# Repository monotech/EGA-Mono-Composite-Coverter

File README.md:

Based on Hugo Holden's "FITTING AN EGA CARD TO AN IBM 5155" from 2016.

This plugs onto an EGA card's feature connector, such as the IBM EGA card.

It adds a crystal clear monochrome composite output in two places, untainted by the colour subcarrier.

* One internal 4-pin header, meant for the IBM 5155's internal amber CRT, which takes a standard composite video input.

* And one at the rear of the EGA card, on one of the usually unconnected RCA jacks.

  * The rear RCA jack output only applies to cards that have this RCA jack connected to the feature connector (P1 on the IBM EGA card: the top RCA jack).

You must set the card to CGA-compatible mode. If the card tries to output EGA-Hi-Res modes, the composite output will be unsupported by most monitors.

Simplified the schematic to reduce BoM and board size.

There is no longer provision for expanding the schematic to add colour-composite.

BoM:

|Designation|Part|
|---|---|
|U1, U2|74HCT86|
|Q1|2N3904|
|C1|4.7 to 10μF|
|C2|100nF|
|P1|2x16 2.54mm male pin header|
|P2|1x4 2.54mm male right-angle pin header|
|R1|75Ω|
|R2, R3|20Ω|
|R4|360Ω|
|R5|110Ω|
|R6|680Ω|
|R7|470Ω|
|R8|2kΩ|
|R9|4.3kΩ|
|R10|1kΩ|

* All parts are through-hole.
* U1 and U2 can be replaced by 74, 74LS, 74S, 74F, 74ACT.
* U2 can be replaced with a 74HCT32 - it will work the same.
* Q1 can be replaced with most general purpose NPN transistors - beware of pinout.
* Resistor tolerances can be 5% or less.
* R2 is only needed for the internal 4-pin header output, intended for IBM 5155.
* R3 is only needed for the rear RCA-jack output (P1 on IBM EGA card).

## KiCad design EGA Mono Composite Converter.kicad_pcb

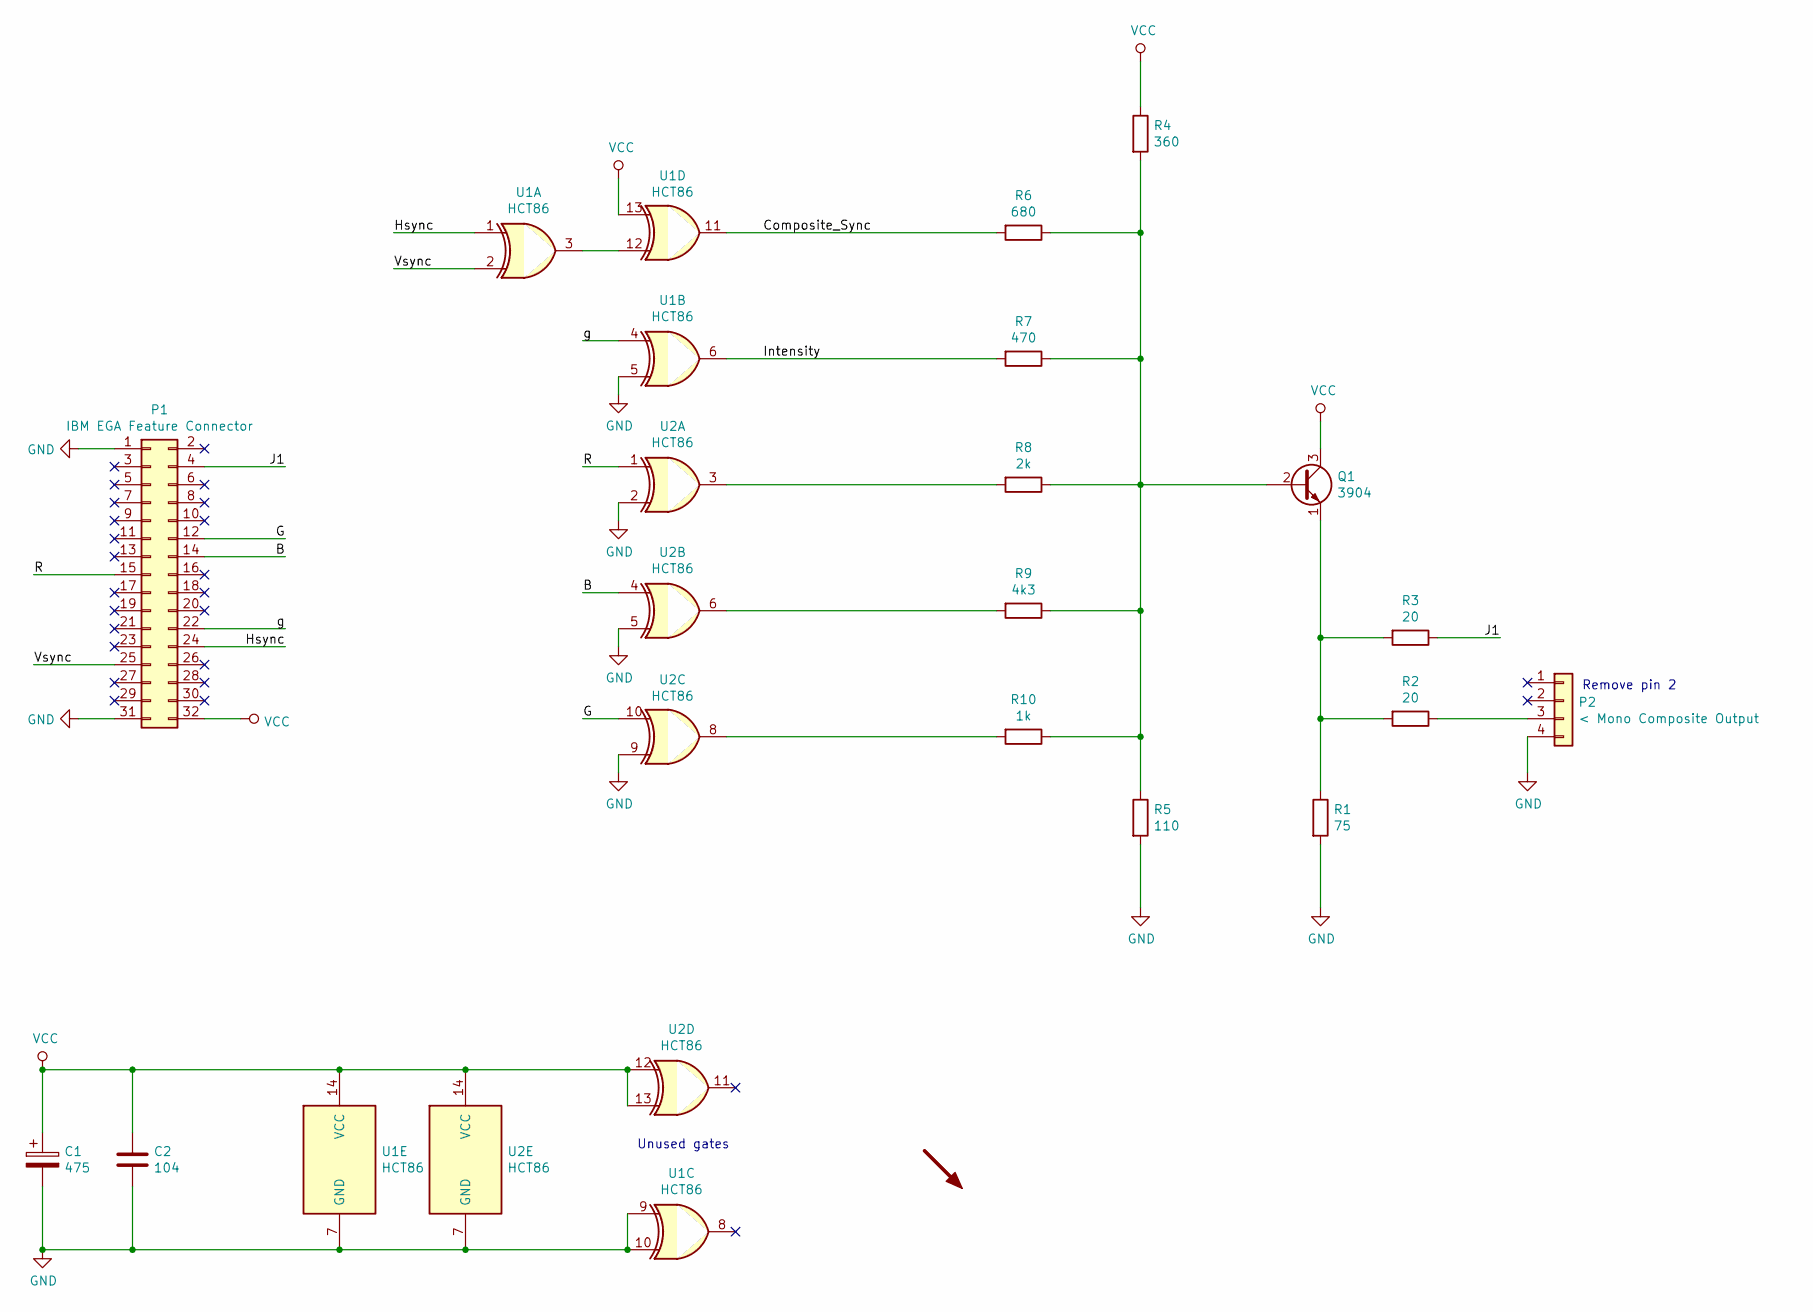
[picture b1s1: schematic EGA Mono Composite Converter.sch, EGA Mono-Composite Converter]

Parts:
C1: 475; C_Disc_D4.3mm_W1.9mm_P5.00mm
C2: 104; C_Axial_L3.8mm_D2.6mm_P7.50mm_Horizontal
LOGO1: SYM_Arrow45_Large; Monotech Logo 12mm
P1: IBM EGA Feature Connector; PinSocket_2x16_P2.54mm_Vertical
P2: < Mono Composite Output; PinHeader_1x04_P2.54mm_Horizontal
Q1: 3904; TO-92_Inline_Wide
R1: 75; R_Axial_DIN0207_L6.3mm_D2.5mm_P10.16mm_Horizontal
R2, R3: 20; R_Axial_DIN0207_L6.3mm_D2.5mm_P10.16mm_Horizontal
R4: 360; R_Axial_DIN0207_L6.3mm_D2.5mm_P10.16mm_Horizontal
R5: 110; R_Axial_DIN0207_L6.3mm_D2.5mm_P10.16mm_Horizontal
R6: 680; R_Axial_DIN0207_L6.3mm_D2.5mm_P10.16mm_Horizontal
R7: 470; R_Axial_DIN0207_L6.3mm_D2.5mm_P10.16mm_Horizontal
R8: 2k; R_Axial_DIN0207_L6.3mm_D2.5mm_P10.16mm_Horizontal
R9: 4k3; R_Axial_DIN0207_L6.3mm_D2.5mm_P10.16mm_Horizontal
R10: 1k; R_Axial_DIN0207_L6.3mm_D2.5mm_P10.16mm_Horizontal
U1, U2: HCT86; DIP-14_W7.62mm

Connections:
/B: P1.14, U2.4
/Composite_Sync: R6.2, U1.11
/G: P1.12, U2.10
/Hsync: P1.24, U1.1
/Intensity: R7.2, U1.6
/J1: P1.4, R3.1
/R: P1.15, U2.1
/Vsync: P1.25, U1.2
/g: P1.22, U1.4
GND: C1.2, C2.2, P1.1, P1.31, P2.4, R1.2, R5.2, U1.5, U1.7 (GND), U1.9, U1.10, U2.2, U2.5, U2.7 (GND), U2.9
unnamed: P2.3, R2.1
unnamed: Q1.1 (E), R1.1, R2.2, R3.2
unnamed: Q1.2 (B), R4.2, R5.1, R6.1, R7.1, R8.1, R9.1, R10.1
unnamed: R8.2, U2.3
unnamed: R9.2, U2.6
unnamed: R10.2, U2.8
unnamed: U1.3, U1.12
VCC: C1.1, C2.1, P1.32, Q1.3 (C), R4.1, U1.13, U1.14 (VCC), U2.12, U2.13, U2.14 (VCC)

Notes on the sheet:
Remove pin 2
Unused gates

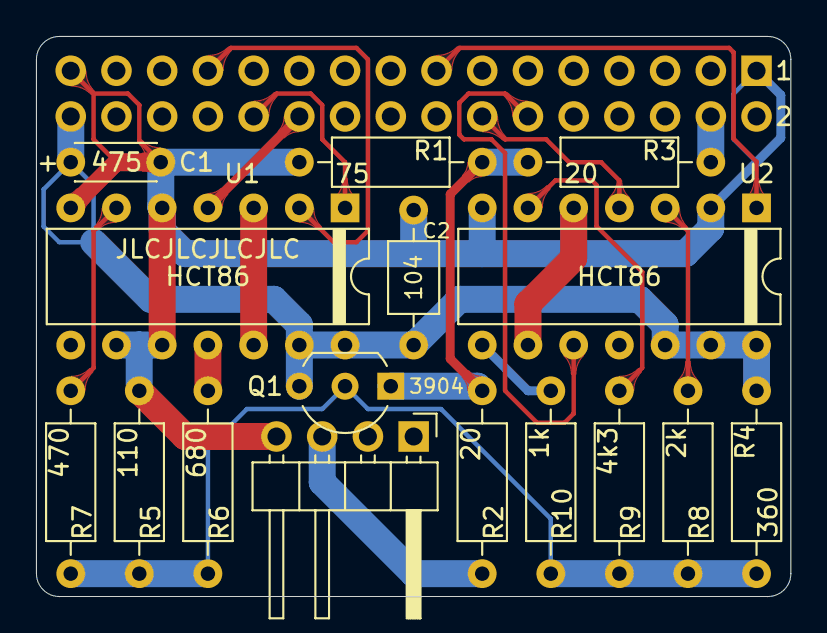
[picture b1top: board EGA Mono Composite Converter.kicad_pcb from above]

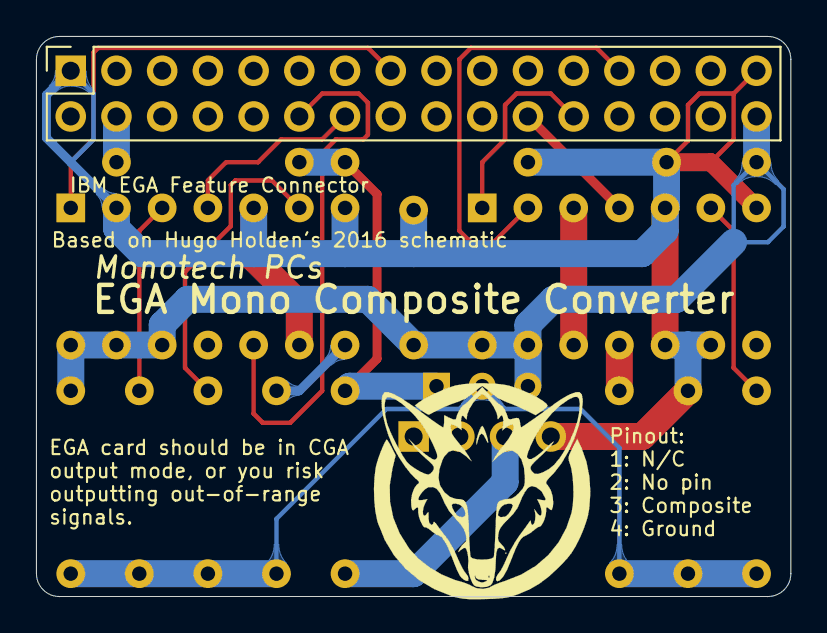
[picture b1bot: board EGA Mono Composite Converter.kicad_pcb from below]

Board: 2 copper layers, 41.9 x 31.1 mm, 18 parts (2 on the bottom side), 18 nets.
